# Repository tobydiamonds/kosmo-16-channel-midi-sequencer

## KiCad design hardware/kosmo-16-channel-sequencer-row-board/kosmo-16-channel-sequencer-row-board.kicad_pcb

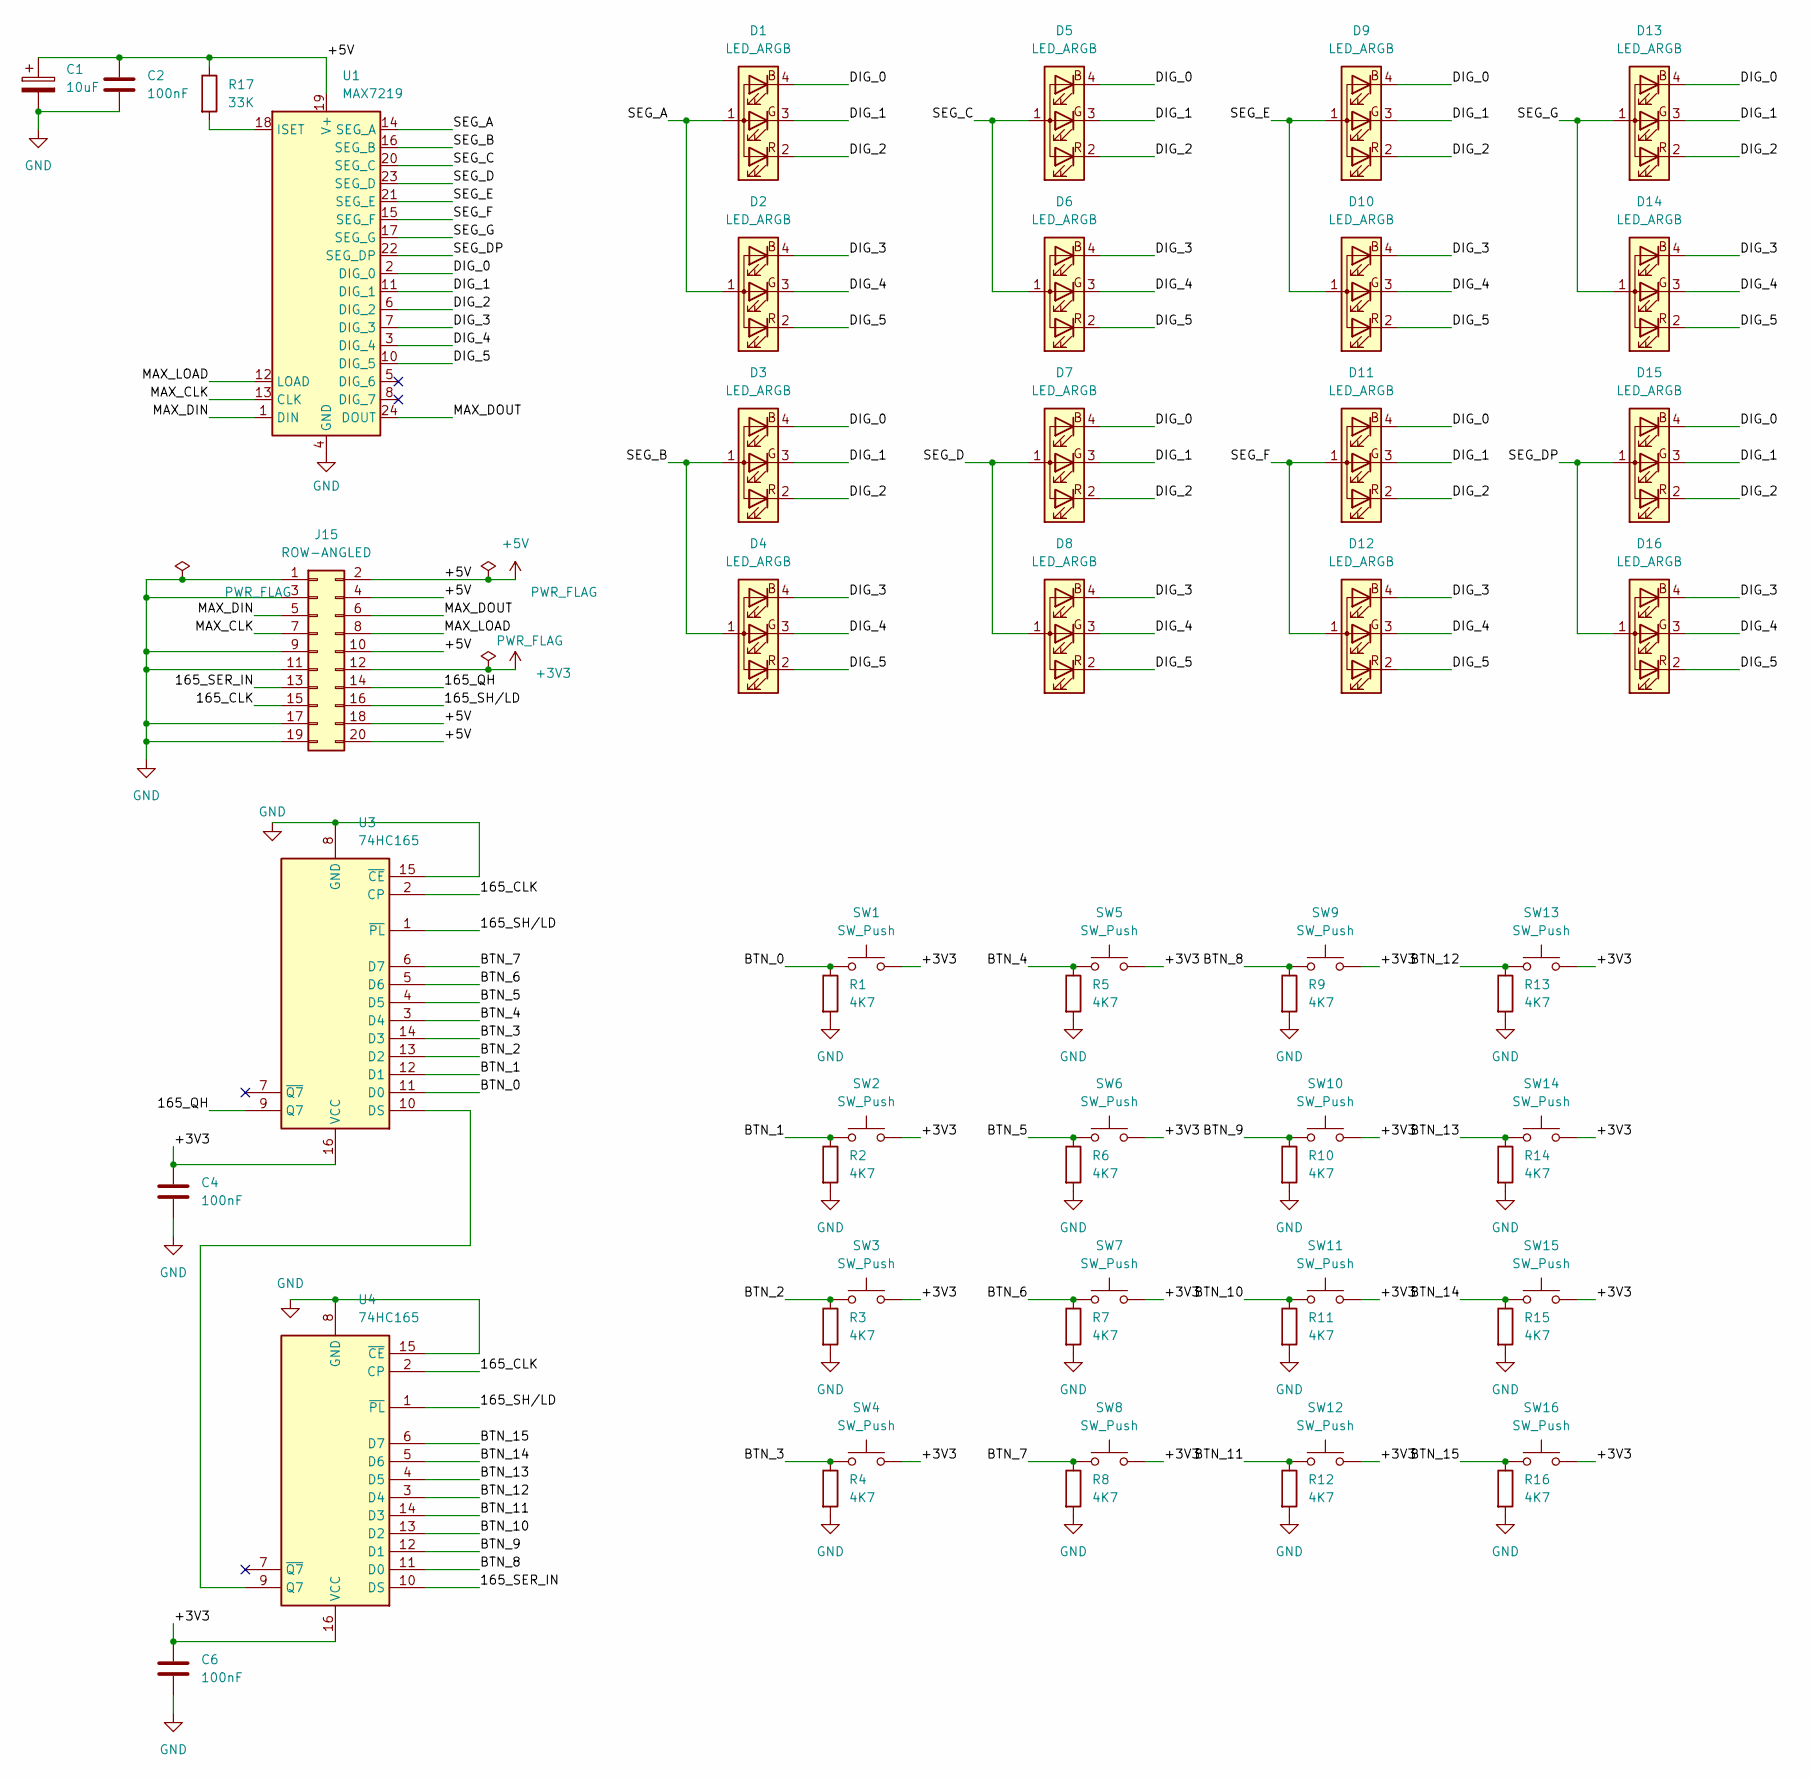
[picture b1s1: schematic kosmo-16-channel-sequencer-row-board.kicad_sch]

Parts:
C1: 10uF; CP_Radial_D6.3mm_P2.50mm
C2, C4, C6: 100nF; C_Disc_D5.0mm_W2.5mm_P5.00mm
D1, D2, D3, D4, D5, D6, D7, D8, D9, D10, D11, D12, D13, D14, D15, D16: LED_ARGB; LED_D5.0mm-4_RGB-common-anode
J15: ROW-ANGLED; PinHeader_2x10_P2.54mm_Vertical
R1, R2, R3, R4, R5, R6, R7, R8, R9, R10, R11, R12, R13, R14, R15, R16: 4K7; R_Axial_DIN0207_L6.3mm_D2.5mm_P7.62mm_Horizontal
R17: 33K; R_Axial_DIN0207_L6.3mm_D2.5mm_P7.62mm_Horizontal
SW1, SW2, SW3, SW4, SW5, SW6, SW7, SW8, SW9, SW10, SW11, SW12, SW13, SW14, SW15, SW16: SW_Push; PinHeader_1x02_P2.54mm_Vertical
U1: MAX7219; SMDIP-24_W15.24mm
U3, U4: 74HC165; DIP-16_W7.62mm

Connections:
+3V3: C4.1, C6.1, J15.12, SW1.2, SW2.2, SW3.2, SW4.2, SW5.2, SW6.2, SW7.2, SW8.2, SW9.2, SW10.2, SW11.2, SW12.2, SW13.2, SW14.2, SW15.2, SW16.2, U3.16 (VCC), U4.16 (VCC)
+5V: C1.1, C2.1, J15.2, J15.4, J15.10, J15.18, J15.20, R17.1, U1.19 (V+)
/165_CLK: J15.15, U3.2 (CP), U4.2 (CP)
/165_QH: J15.14, U3.9 (Q7)
/165_SER_IN: J15.13, U4.10 (DS)
/165_SH/LD: J15.16, U3.1 (~PL), U4.1 (~PL)
/BTN_0: R1.1, SW1.1, U3.11 (D0)
/BTN_1: R2.1, SW2.1, U3.12 (D1)
/BTN_2: R3.1, SW3.1, U3.13 (D2)
/BTN_3: R4.1, SW4.1, U3.14 (D3)
/BTN_4: R5.1, SW5.1, U3.3 (D4)
/BTN_5: R6.1, SW6.1, U3.4 (D5)
/BTN_6: R7.1, SW7.1, U3.5 (D6)
/BTN_7: R8.1, SW8.1, U3.6 (D7)
/BTN_8: R9.1, SW9.1, U4.11 (D0)
/BTN_9: R10.1, SW10.1, U4.12 (D1)
/BTN_10: R11.1, SW11.1, U4.13 (D2)
/BTN_11: R12.1, SW12.1, U4.14 (D3)
/BTN_12: R13.1, SW13.1, U4.3 (D4)
/BTN_13: R14.1, SW14.1, U4.4 (D5)
/BTN_14: R15.1, SW15.1, U4.5 (D6)
/BTN_15: R16.1, SW16.1, U4.6 (D7)
/DIG_0: D1.4 (BK), D3.4 (BK), D5.4 (BK), D7.4 (BK), D9.4 (BK), D11.4 (BK), D13.4 (BK), D15.4 (BK), U1.2 (DIG_0)
/DIG_1: D1.3 (GK), D3.3 (GK), D5.3 (GK), D7.3 (GK), D9.3 (GK), D11.3 (GK), D13.3 (GK), D15.3 (GK), U1.11 (DIG_1)
/DIG_2: D1.2 (RK), D3.2 (RK), D5.2 (RK), D7.2 (RK), D9.2 (RK), D11.2 (RK), D13.2 (RK), D15.2 (RK), U1.6 (DIG_2)
/DIG_3: D2.4 (BK), D4.4 (BK), D6.4 (BK), D8.4 (BK), D10.4 (BK), D12.4 (BK), D14.4 (BK), D16.4 (BK), U1.7 (DIG_3)
/DIG_4: D2.3 (GK), D4.3 (GK), D6.3 (GK), D8.3 (GK), D10.3 (GK), D12.3 (GK), D14.3 (GK), D16.3 (GK), U1.3 (DIG_4)
/DIG_5: D2.2 (RK), D4.2 (RK), D6.2 (RK), D8.2 (RK), D10.2 (RK), D12.2 (RK), D14.2 (RK), D16.2 (RK), U1.10 (DIG_5)
/MAX_CLK: J15.7, U1.13 (CLK)
/MAX_DIN: J15.5, U1.1 (DIN)
/MAX_DOUT: J15.6, U1.24 (DOUT)
/MAX_LOAD: J15.8, U1.12 (LOAD)
/SEG_A: D1.1 (A), D2.1 (A), U1.14 (SEG_A)
/SEG_B: D3.1 (A), D4.1 (A), U1.16 (SEG_B)
/SEG_C: D5.1 (A), D6.1 (A), U1.20 (SEG_C)
/SEG_D: D7.1 (A), D8.1 (A), U1.23 (SEG_D)
/SEG_DP: D15.1 (A), D16.1 (A), U1.22 (SEG_DP)
/SEG_E: D9.1 (A), D10.1 (A), U1.21 (SEG_E)
/SEG_F: D11.1 (A), D12.1 (A), U1.15 (SEG_F)
/SEG_G: D13.1 (A), D14.1 (A), U1.17 (SEG_G)
GND: C1.2, C2.2, C4.2, C6.2, J15.1, J15.3, J15.9, J15.11, J15.17, J15.19, R1.2, R2.2, R3.2, R4.2, R5.2, R6.2, R7.2, R8.2, R9.2, R10.2, R11.2, R12.2, R13.2, R14.2, R15.2, R16.2, U1.4 (GND), U1.9 (GND), U3.8 (GND), U3.15 (~CE), U4.8 (GND), U4.15 (~CE)
unnamed: R17.2, U1.18 (ISET)
unnamed: U3.10 (DS), U4.9 (Q7)

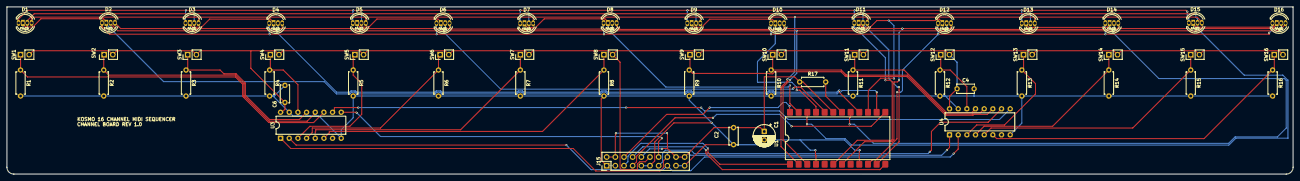
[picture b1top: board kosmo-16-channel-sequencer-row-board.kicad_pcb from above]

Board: 2 copper layers, 377.0 x 49.0 mm, 57 parts (0 on the bottom side), 43 nets.

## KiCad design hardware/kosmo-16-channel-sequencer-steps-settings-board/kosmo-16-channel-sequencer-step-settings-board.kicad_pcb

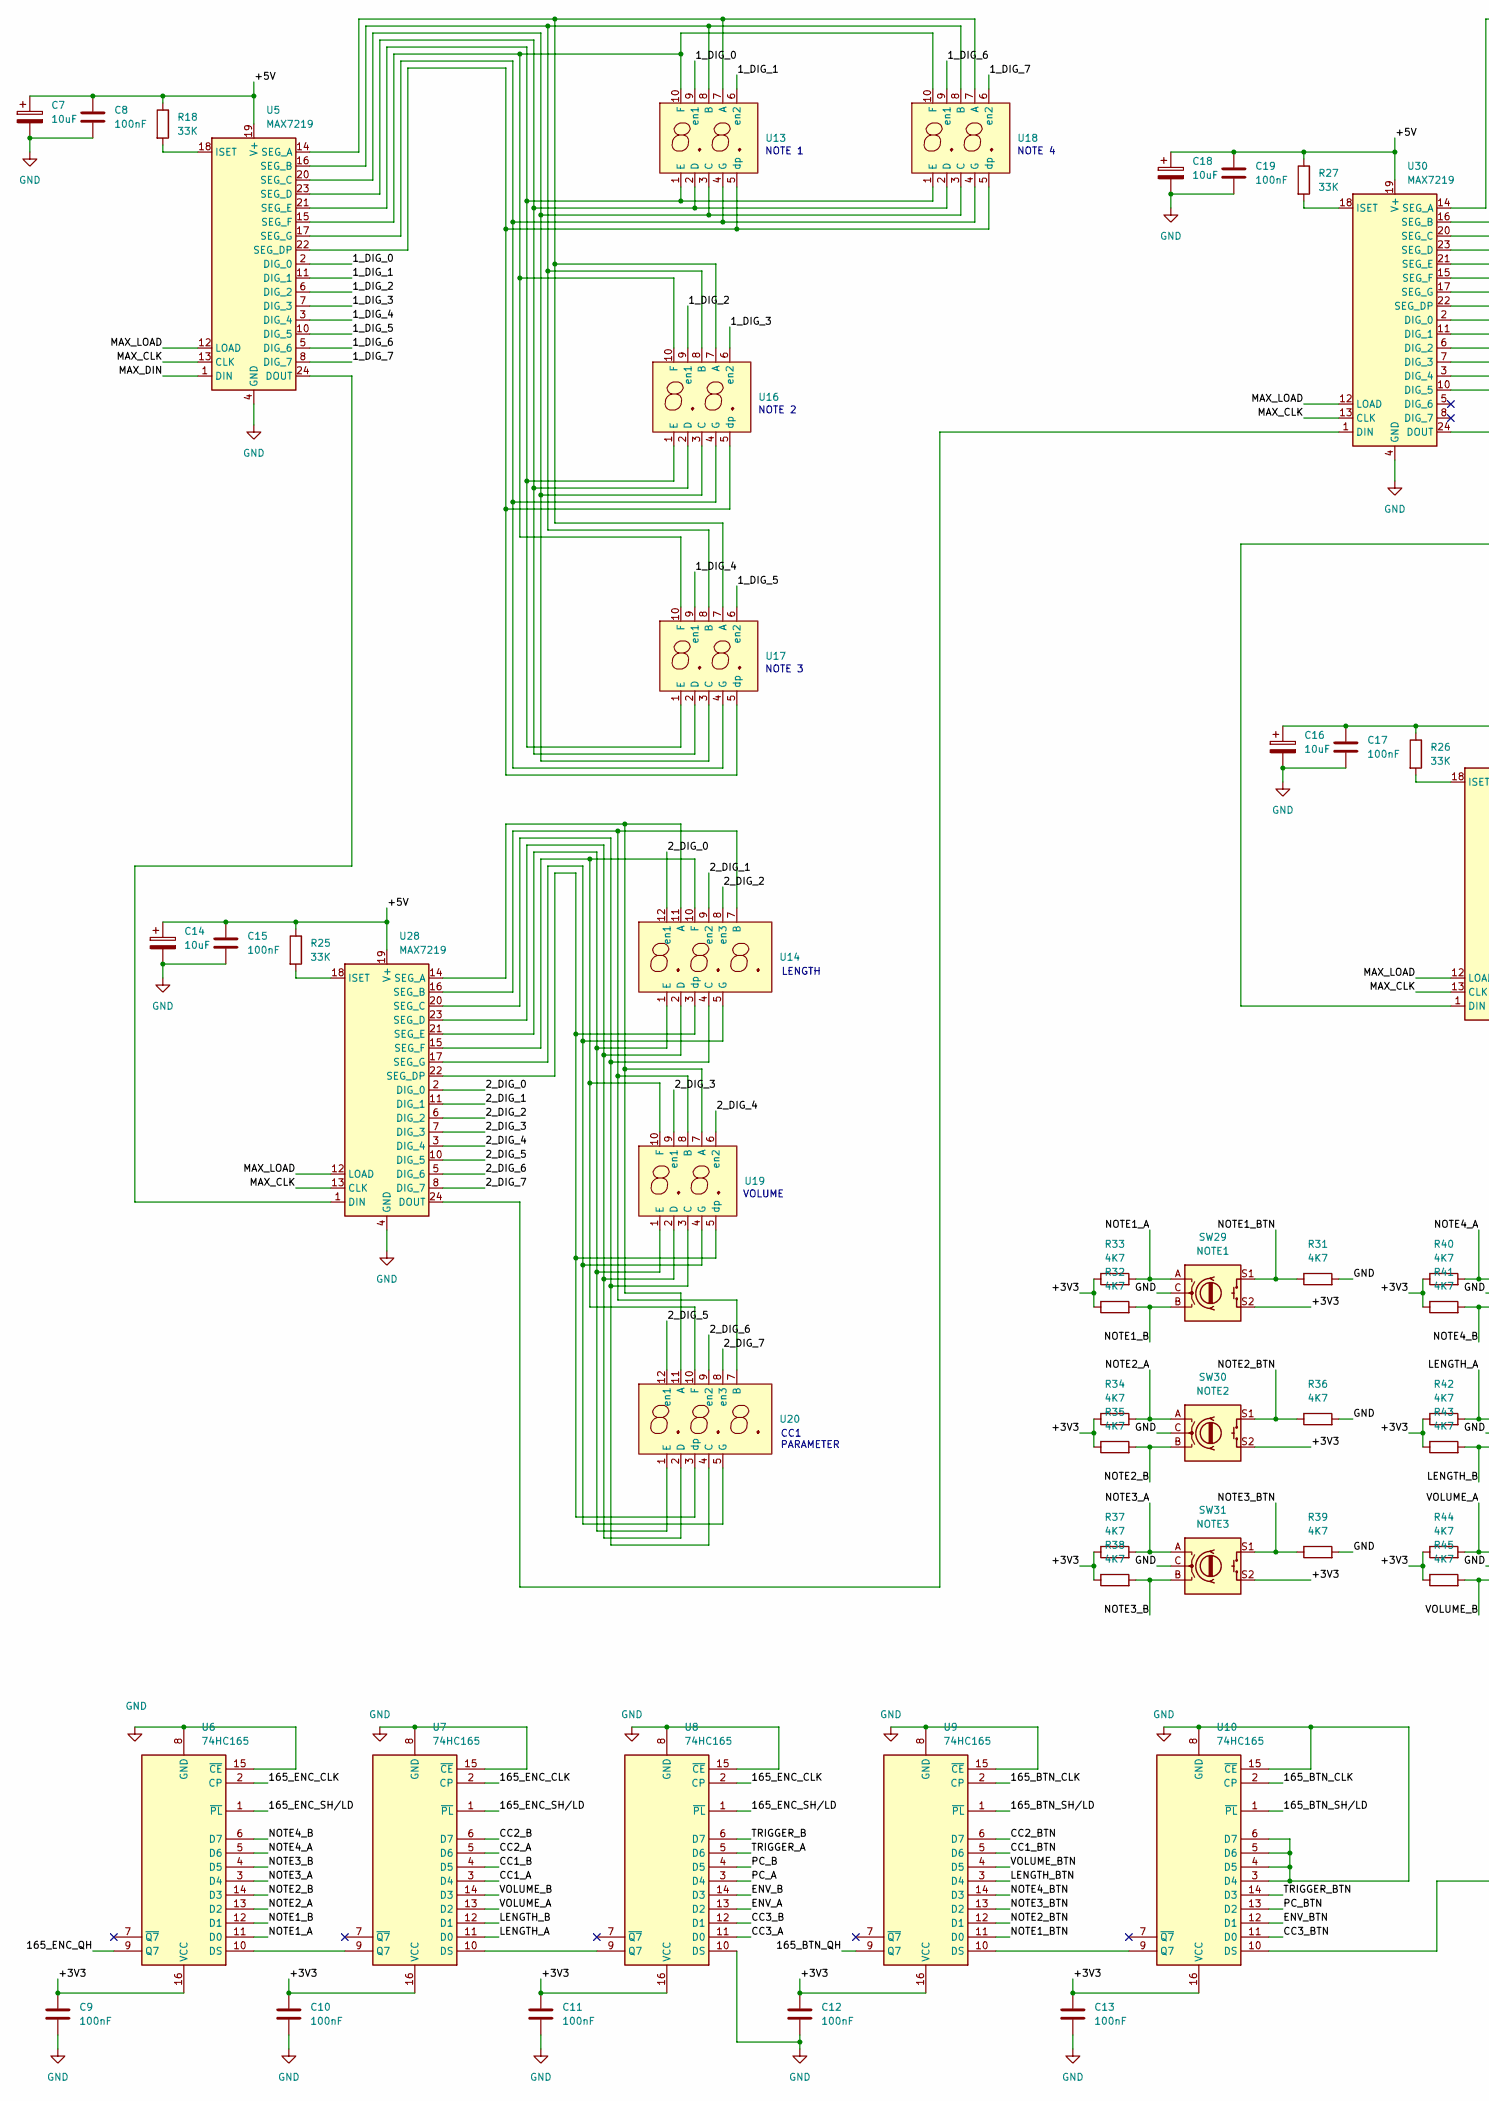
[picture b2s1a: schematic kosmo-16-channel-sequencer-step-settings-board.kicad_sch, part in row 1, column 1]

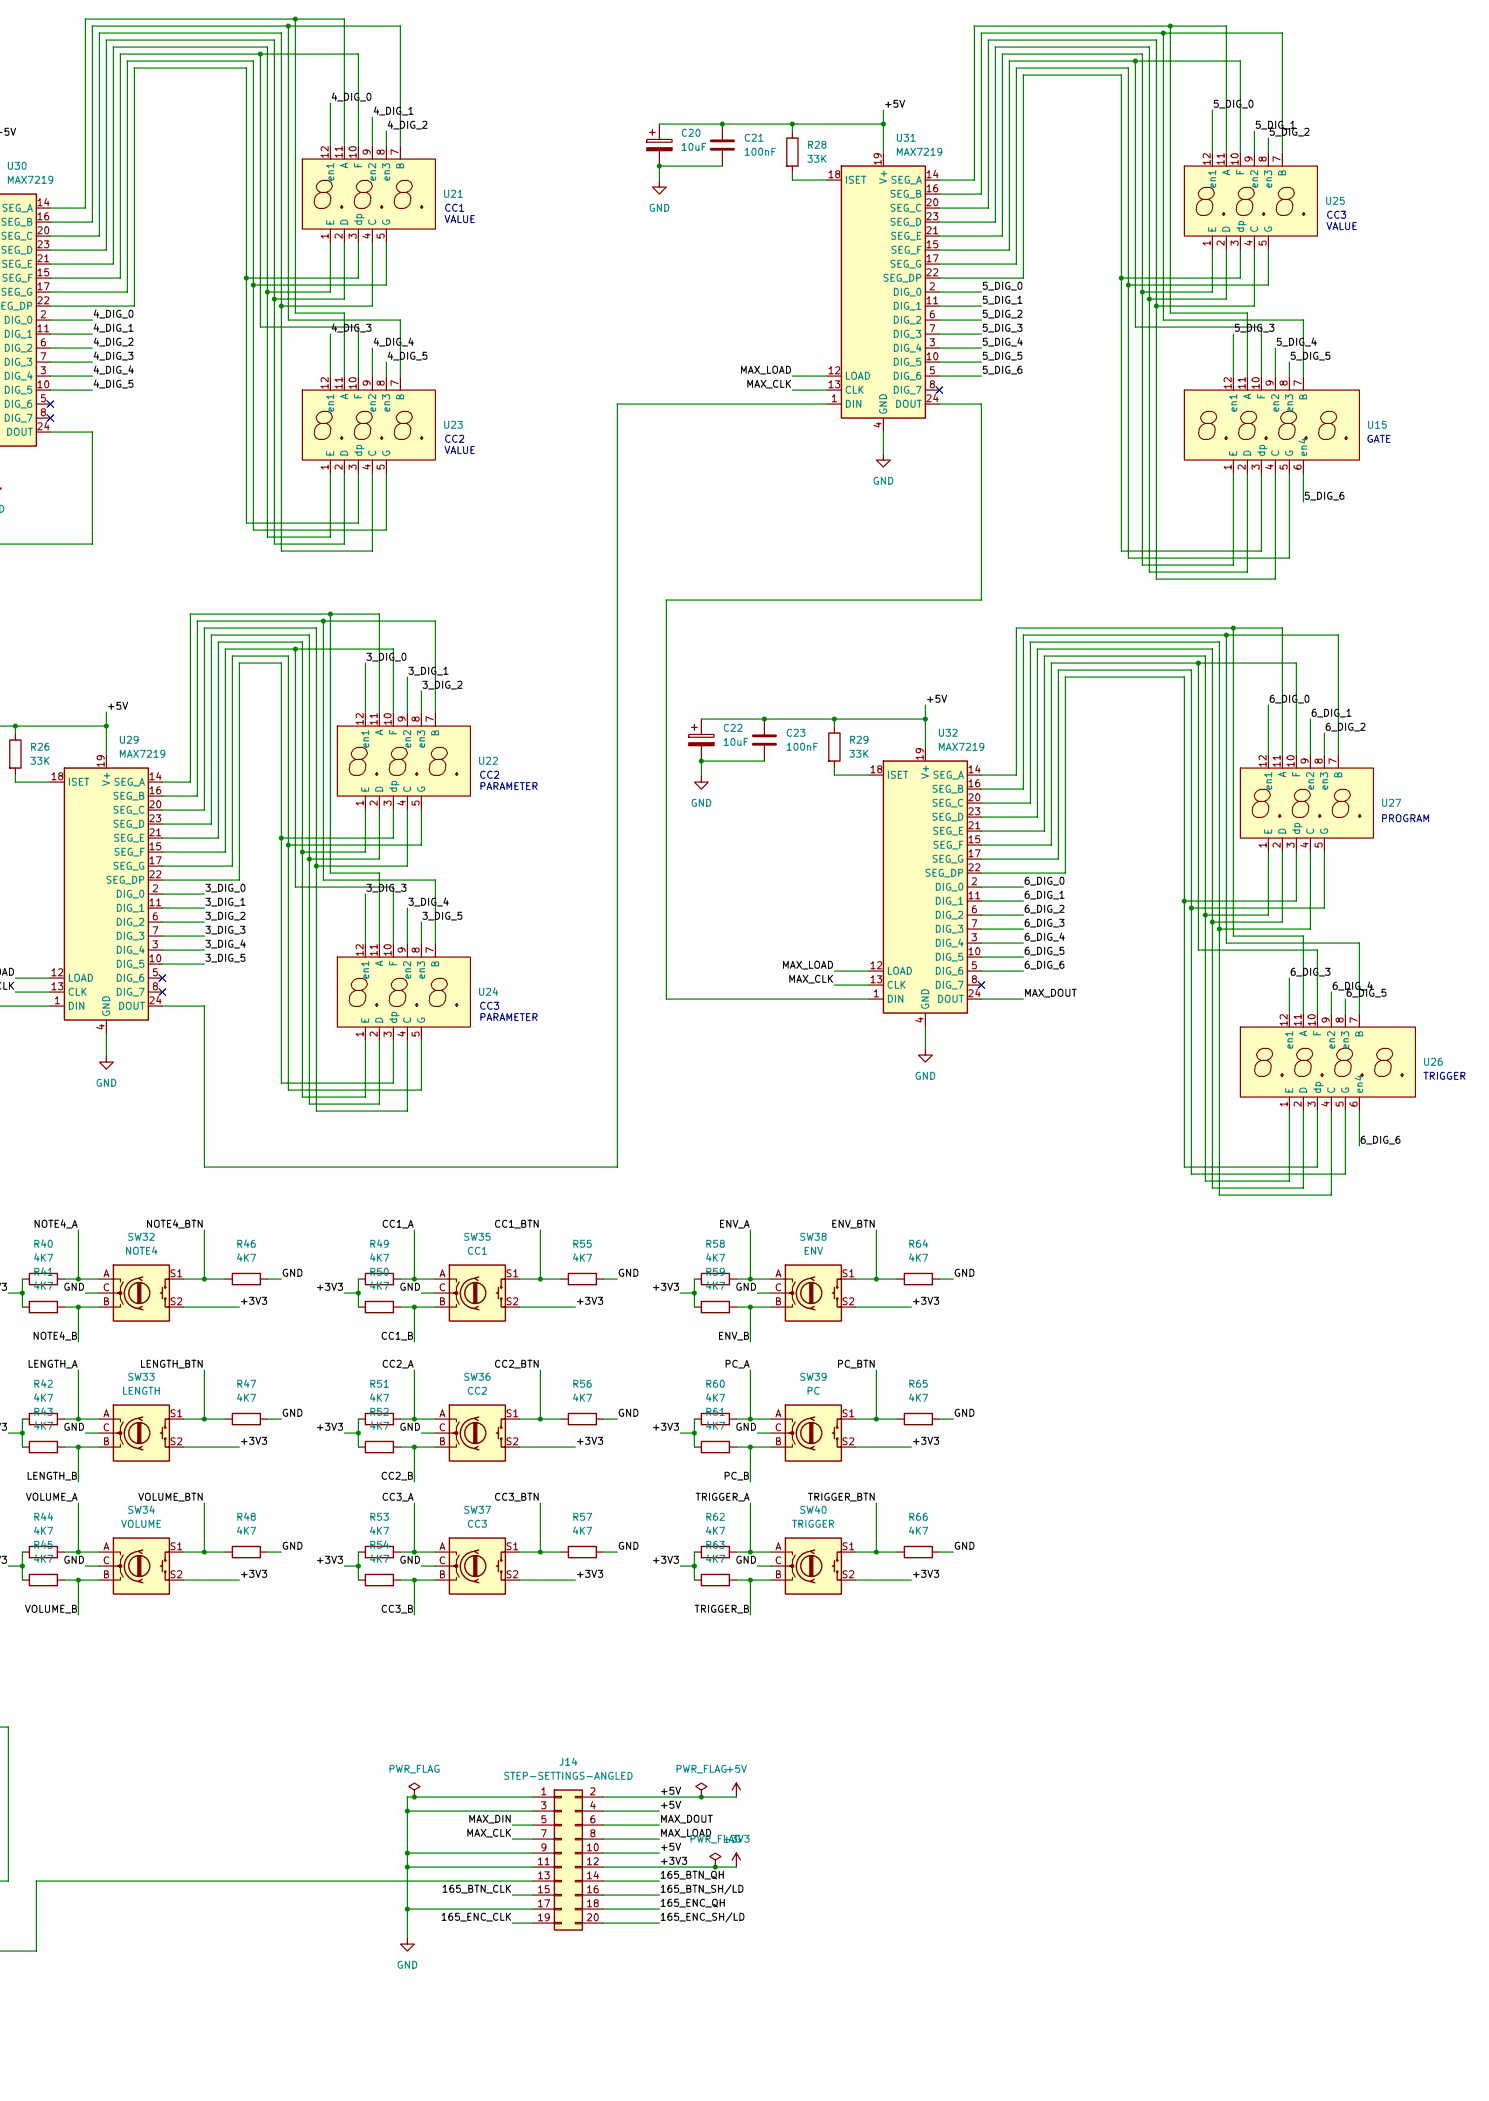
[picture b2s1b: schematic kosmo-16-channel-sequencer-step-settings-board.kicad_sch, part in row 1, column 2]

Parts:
C7, C14, C16, C18, C20, C22: 10uF; CP_Radial_D6.3mm_P2.50mm
C8, C9, C10, C11, C12, C13, C15, C17, C19, C21, C23: 100nF; C_Disc_D5.0mm_W2.5mm_P5.00mm
J14: STEP-SETTINGS-ANGLED; PinHeader_2x10_P2.54mm_Vertical
R18, R25, R26, R27, R28, R29: 33K; R_Axial_DIN0207_L6.3mm_D2.5mm_P7.62mm_Horizontal
R31, R32, R33, R34, R35, R36, R37, R38, R39, R40, R41, R42, R43, R44, R45, R46, R47, R48, R49, R50, R51, R52, R53, R54, R55, R56, R57, R58, R59, R60, R61, R62, R63, R64, R65, R66: 4K7; R_Axial_DIN0207_L6.3mm_D2.5mm_P7.62mm_Horizontal
SW29: NOTE1; RotaryEncoder_Bourns_Vertical_PEC12R-3x17F-Sxxxx
SW30: NOTE2; RotaryEncoder_Bourns_Vertical_PEC12R-3x17F-Sxxxx
SW31: NOTE3; RotaryEncoder_Bourns_Vertical_PEC12R-3x17F-Sxxxx
SW32: NOTE4; RotaryEncoder_Bourns_Vertical_PEC12R-3x17F-Sxxxx
SW33: LENGTH; RotaryEncoder_Bourns_Vertical_PEC12R-3x17F-Sxxxx
SW34: VOLUME; RotaryEncoder_Bourns_Vertical_PEC12R-3x17F-Sxxxx
SW35: CC1; RotaryEncoder_Bourns_Vertical_PEC12R-3x17F-Sxxxx
SW36: CC2; RotaryEncoder_Bourns_Vertical_PEC12R-3x17F-Sxxxx
SW37: CC3; RotaryEncoder_Bourns_Vertical_PEC12R-3x17F-Sxxxx
SW38: ENV; RotaryEncoder_Bourns_Vertical_PEC12R-3x17F-Sxxxx
SW39: PC; RotaryEncoder_Bourns_Vertical_PEC12R-3x17F-Sxxxx
SW40: TRIGGER; RotaryEncoder_Bourns_Vertical_PEC12R-3x17F-Sxxxx
U5, U28, U29, U30, U31, U32: MAX7219; SMDIP-24_W15.24mm
U6, U7, U8, U9, U10: 74HC165; DIP-16_W7.62mm
U13, U16, U17, U18, U19: DIP-10_W7.62mm
U14, U15, U20, U21, U22, U23, U24, U25, U26, U27: DIP-12_W7.62mm

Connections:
+3V3: C9.1, C10.1, C11.1, C12.1, C13.1, J14.12, R32.1, R33.1, R34.1, R35.1, R37.1, R38.1, R40.1, R41.1, R42.1, R43.1, R44.1, R45.1, R49.1, R50.1, R51.1, R52.1, R53.1, R54.1, R58.1, R59.1, R60.1, R61.1, R62.1, R63.1, SW29.S2, SW30.S2, SW31.S2, SW32.S2, SW33.S2, SW34.S2, SW35.S2, SW36.S2, SW37.S2, SW38.S2, SW39.S2, SW40.S2, U6.16 (VCC), U7.16 (VCC), U8.16 (VCC), U9.16 (VCC), U10.16 (VCC)
+5V: C7.1, C8.1, C14.1, C15.1, C16.1, C17.1, C18.1, C19.1, C20.1, C21.1, C22.1, C23.1, J14.2, J14.4, J14.10, R18.1, R25.1, R26.1, R27.1, R28.1, R29.1, U5.19 (V+), U28.19 (V+), U29.19 (V+), U30.19 (V+), U31.19 (V+), U32.19 (V+)
/1_DIG_0: U5.2 (DIG_0), U13.9 (en1)
/1_DIG_1: U5.11 (DIG_1), U13.6 (en2)
/1_DIG_2: U5.6 (DIG_2), U16.9 (en1)
/1_DIG_3: U5.7 (DIG_3), U16.6 (en2)
/1_DIG_4: U5.3 (DIG_4), U17.9 (en1)
/1_DIG_5: U5.10 (DIG_5), U17.6 (en2)
/1_DIG_6: U5.5 (DIG_6), U18.9 (en1)
/1_DIG_7: U5.8 (DIG_7), U18.6 (en2)
/2_DIG_0: U14.12 (en1), U28.2 (DIG_0)
/2_DIG_1: U14.9 (en2), U28.11 (DIG_1)
/2_DIG_2: U14.8 (en3), U28.6 (DIG_2)
/2_DIG_3: U19.9 (en1), U28.7 (DIG_3)
/2_DIG_4: U19.6 (en2), U28.3 (DIG_4)
/2_DIG_5: U20.12 (en1), U28.10 (DIG_5)
/2_DIG_6: U20.9 (en2), U28.5 (DIG_6)
/2_DIG_7: U20.8 (en3), U28.8 (DIG_7)
/3_DIG_0: U22.12 (en1), U29.2 (DIG_0)
/3_DIG_1: U22.9 (en2), U29.11 (DIG_1)
/3_DIG_2: U22.8 (en3), U29.6 (DIG_2)
/3_DIG_3: U24.12 (en1), U29.7 (DIG_3)
/3_DIG_4: U24.9 (en2), U29.3 (DIG_4)
/3_DIG_5: U24.8 (en3), U29.10 (DIG_5)
/4_DIG_0: U21.12 (en1), U30.2 (DIG_0)
/4_DIG_1: U21.9 (en2), U30.11 (DIG_1)
/4_DIG_2: U21.8 (en3), U30.6 (DIG_2)
/4_DIG_3: U23.12 (en1), U30.7 (DIG_3)
/4_DIG_4: U23.9 (en2), U30.3 (DIG_4)
/4_DIG_5: U23.8 (en3), U30.10 (DIG_5)
/5_DIG_0: U25.12 (en1), U31.2 (DIG_0)
/5_DIG_1: U25.9 (en2), U31.11 (DIG_1)
/5_DIG_2: U25.8 (en3), U31.6 (DIG_2)
/5_DIG_3: U15.12 (en1), U31.7 (DIG_3)
/5_DIG_4: U15.9 (en2), U31.3 (DIG_4)
/5_DIG_5: U15.8 (en3), U31.10 (DIG_5)
/5_DIG_6: U15.6 (en4), U31.5 (DIG_6)
/6_DIG_0: U27.12 (en1), U32.2 (DIG_0)
/6_DIG_1: U27.9 (en2), U32.11 (DIG_1)
/6_DIG_2: U27.8 (en3), U32.6 (DIG_2)
/6_DIG_3: U26.12 (en1), U32.7 (DIG_3)
/6_DIG_4: U26.9 (en2), U32.3 (DIG_4)
/6_DIG_5: U26.8 (en3), U32.10 (DIG_5)
/6_DIG_6: U26.6 (en4), U32.5 (DIG_6)
/165_BTN_CLK: J14.15, U9.2 (CP), U10.2 (CP)
/165_BTN_QH: J14.14, U9.9 (Q7)
/165_BTN_SH/LD: J14.16, U9.1 (~PL), U10.1 (~PL)
/165_ENC_CLK: J14.19, U6.2 (CP), U7.2 (CP), U8.2 (CP)
/165_ENC_QH: J14.18, U6.9 (Q7)
/165_ENC_SH/LD: J14.20, U6.1 (~PL), U7.1 (~PL), U8.1 (~PL)
/CC1_A: R49.2, SW35.A, U7.3 (D4)
/CC1_B: R50.2, SW35.B, U7.4 (D5)
/CC1_BTN: R55.1, SW35.S1, U9.5 (D6)
/CC2_A: R51.2, SW36.A, U7.5 (D6)
/CC2_B: R52.2, SW36.B, U7.6 (D7)
/CC2_BTN: R56.1, SW36.S1, U9.6 (D7)
/CC3_A: R53.2, SW37.A, U8.11 (D0)
/CC3_B: R54.2, SW37.B, U8.12 (D1)
/CC3_BTN: R57.1, SW37.S1, U10.11 (D0)
/ENV_A: R58.2, SW38.A, U8.13 (D2)
/ENV_B: R59.2, SW38.B, U8.14 (D3)
/ENV_BTN: R64.1, SW38.S1, U10.12 (D1)
/LENGTH_A: R42.2, SW33.A, U7.11 (D0)
/LENGTH_B: R43.2, SW33.B, U7.12 (D1)
/LENGTH_BTN: R47.1, SW33.S1, U9.3 (D4)
/MAX_CLK: J14.7, U5.13 (CLK), U28.13 (CLK), U29.13 (CLK), U30.13 (CLK), U31.13 (CLK), U32.13 (CLK)
/MAX_DIN: J14.5, U5.1 (DIN)
/MAX_DOUT: J14.6, U32.24 (DOUT)
/MAX_LOAD: J14.8, U5.12 (LOAD), U28.12 (LOAD), U29.12 (LOAD), U30.12 (LOAD), U31.12 (LOAD), U32.12 (LOAD)
/NOTE1_A: R33.2, SW29.A, U6.11 (D0)
/NOTE1_B: R32.2, SW29.B, U6.12 (D1)
/NOTE1_BTN: R31.1, SW29.S1, U9.11 (D0)
/NOTE2_A: R34.2, SW30.A, U6.13 (D2)
/NOTE2_B: R35.2, SW30.B, U6.14 (D3)
/NOTE2_BTN: R36.1, SW30.S1, U9.12 (D1)
/NOTE3_A: R37.2, SW31.A, U6.3 (D4)
/NOTE3_B: R38.2, SW31.B, U6.4 (D5)
/NOTE3_BTN: R39.1, SW31.S1, U9.13 (D2)
/NOTE4_A: R40.2, SW32.A, U6.5 (D6)
/NOTE4_B: R41.2, SW32.B, U6.6 (D7)
/NOTE4_BTN: R46.1, SW32.S1, U9.14 (D3)
/PC_A: R60.2, SW39.A, U8.3 (D4)
/PC_B: R61.2, SW39.B, U8.4 (D5)
/PC_BTN: R65.1, SW39.S1, U10.13 (D2)
/TRIGGER_A: R62.2, SW40.A, U8.5 (D6)
/TRIGGER_B: R63.2, SW40.B, U8.6 (D7)
/TRIGGER_BTN: R66.1, SW40.S1, U10.14 (D3)
/VOLUME_A: R44.2, SW34.A, U7.13 (D2)
/VOLUME_B: R45.2, SW34.B, U7.14 (D3)
/VOLUME_BTN: R48.1, SW34.S1, U9.4 (D5)
GND: C7.2, C8.2, C9.2, C10.2, C11.2, C12.2, C13.2, C14.2, C15.2, C16.2, C17.2, C18.2, C19.2, C20.2, C21.2, C22.2, C23.2, J14.1, J14.3, J14.9, J14.11, J14.17, R31.2, R36.2, R39.2, R46.2, R47.2, R48.2, R55.2, R56.2, R57.2, R64.2, R65.2, R66.2, SW29.C, SW30.C, SW31.C, SW32.C, SW33.C, SW34.C, SW35.C, SW36.C, SW37.C, SW38.C, SW39.C, SW40.C, U5.4 (GND), U5.9 (GND), U6.8 (GND), U6.15 (~CE), U7.8 (GND), U7.15 (~CE), U8.8 (GND), U8.10 (DS), U8.15 (~CE), U9.8 (GND), U9.15 (~CE), U10.3 (D4), U10.4 (D5), U10.5 (D6), U10.6 (D7), U10.8 (GND), U10.15 (~CE), U28.4 (GND), U28.9 (GND), U29.4 (GND), U29.9 (GND), U30.4 (GND), U30.9 (GND), U31.4 (GND), U31.9 (GND), U32.4 (GND), U32.9 (GND)
unnamed: J14.13, U10.10 (DS)
unnamed: R18.2, U5.18 (ISET)
unnamed: U6.10 (DS), U7.9 (Q7)
unnamed: U7.10 (DS), U8.9 (Q7)
unnamed: U9.10 (DS), U10.9 (Q7)
unnamed: U5.14 (SEG_A), U13.7 (A), U16.7 (A), U17.7 (A), U18.7 (A)
unnamed: U5.16 (SEG_B), U13.8 (B), U16.8 (B), U17.8 (B), U18.8 (B)
unnamed: U5.20 (SEG_C), U13.3 (C), U16.3 (C), U17.3 (C), U18.3 (C)
unnamed: U5.23 (SEG_D), U13.2 (D), U16.2 (D), U17.2 (D), U18.2 (D)
unnamed: U5.21 (SEG_E), U13.1 (E), U16.1 (E), U17.1 (E), U18.1 (E)
unnamed: U5.15 (SEG_F), U13.10 (F), U16.10 (F), U17.10 (F), U18.10 (F)
unnamed: U5.17 (SEG_G), U13.4 (G), U16.4 (G), U17.4 (G), U18.4 (G)
unnamed: U5.22 (SEG_DP), U13.5 (dp), U16.5 (dp), U17.5 (dp), U18.5 (dp)
unnamed: U14.11 (A), U19.7 (A), U20.11 (A), U28.14 (SEG_A)
unnamed: U14.7 (B), U19.8 (B), U20.7 (B), U28.16 (SEG_B)
unnamed: U14.4 (C), U19.3 (C), U20.4 (C), U28.20 (SEG_C)
unnamed: U14.2 (D), U19.2 (D), U20.2 (D), U28.23 (SEG_D)
unnamed: U14.1 (E), U19.1 (E), U20.1 (E), U28.21 (SEG_E)
unnamed: U14.10 (F), U19.10 (F), U20.10 (F), U28.15 (SEG_F)
unnamed: U14.5 (G), U19.4 (G), U20.5 (G), U28.17 (SEG_G)
unnamed: U14.3 (dp), U19.5 (dp), U20.3 (dp), U28.22 (SEG_DP)
unnamed: U15.11 (A), U25.11 (A), U31.14 (SEG_A)
unnamed: U15.7 (B), U25.7 (B), U31.16 (SEG_B)
unnamed: U15.4 (C), U25.4 (C), U31.20 (SEG_C)
unnamed: U15.2 (D), U25.2 (D), U31.23 (SEG_D)
unnamed: U15.1 (E), U25.1 (E), U31.21 (SEG_E)
unnamed: U15.10 (F), U25.10 (F), U31.15 (SEG_F)
unnamed: U15.5 (G), U25.5 (G), U31.17 (SEG_G)
unnamed: U15.3 (dp), U25.3 (dp), U31.22 (SEG_DP)
unnamed: U21.11 (A), U23.11 (A), U30.14 (SEG_A)
unnamed: U21.7 (B), U23.7 (B), U30.16 (SEG_B)
unnamed: U21.4 (C), U23.4 (C), U30.20 (SEG_C)
unnamed: U21.2 (D), U23.2 (D), U30.23 (SEG_D)
unnamed: U21.1 (E), U23.1 (E), U30.21 (SEG_E)
unnamed: U21.10 (F), U23.10 (F), U30.15 (SEG_F)
unnamed: U21.5 (G), U23.5 (G), U30.17 (SEG_G)
unnamed: U21.3 (dp), U23.3 (dp), U30.22 (SEG_DP)
unnamed: U22.11 (A), U24.11 (A), U29.14 (SEG_A)
unnamed: U22.7 (B), U24.7 (B), U29.16 (SEG_B)
unnamed: U22.4 (C), U24.4 (C), U29.20 (SEG_C)
unnamed: U22.2 (D), U24.2 (D), U29.23 (SEG_D)
unnamed: U22.1 (E), U24.1 (E), U29.21 (SEG_E)
unnamed: U22.10 (F), U24.10 (F), U29.15 (SEG_F)
unnamed: U22.5 (G), U24.5 (G), U29.17 (SEG_G)
unnamed: U22.3 (dp), U24.3 (dp), U29.22 (SEG_DP)
unnamed: U26.11 (A), U27.11 (A), U32.14 (SEG_A)
unnamed: U26.7 (B), U27.7 (B), U32.16 (SEG_B)
unnamed: U26.4 (C), U27.4 (C), U32.20 (SEG_C)
unnamed: U26.2 (D), U27.2 (D), U32.23 (SEG_D)
unnamed: U26.1 (E), U27.1 (E), U32.21 (SEG_E)
unnamed: U26.10 (F), U27.10 (F), U32.15 (SEG_F)
unnamed: U26.5 (G), U27.5 (G), U32.17 (SEG_G)
unnamed: U26.3 (dp), U27.3 (dp), U32.22 (SEG_DP)
unnamed: U5.24 (DOUT), U28.1 (DIN)
unnamed: U28.24 (DOUT), U30.1 (DIN)
unnamed: R25.2, U28.18 (ISET)
unnamed: U29.1 (DIN), U30.24 (DOUT)
unnamed: U29.24 (DOUT), U31.1 (DIN)
unnamed: R26.2, U29.18 (ISET)
unnamed: R27.2, U30.18 (ISET)
unnamed: U31.24 (DOUT), U32.1 (DIN)
unnamed: R28.2, U31.18 (ISET)
unnamed: R29.2, U32.18 (ISET)

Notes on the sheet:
GATE
NOTE 4
NOTE 1
CC1 PARAMETER
NOTE 2
VOLUME
CC3 VALUE
PROGRAM
CC3 PARAMETER
TRIGGER
LENGTH
CC2 VALUE
CC1 VALUE
NOTE 3
CC2 PARAMETER

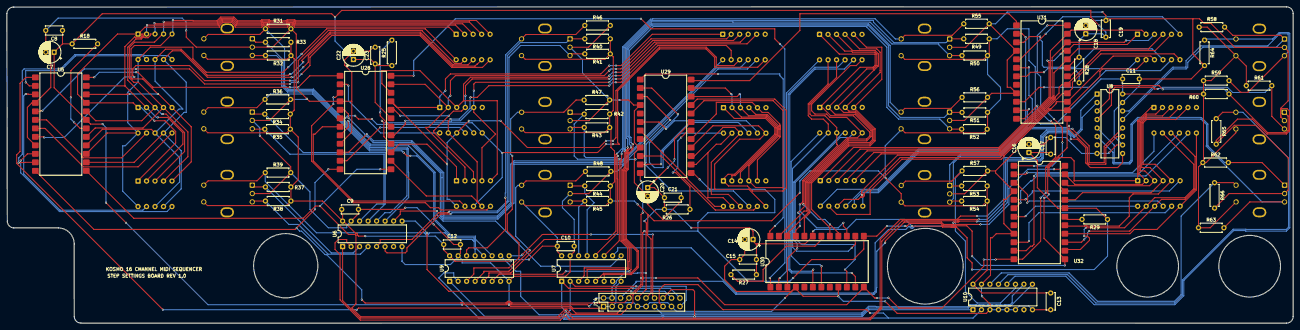
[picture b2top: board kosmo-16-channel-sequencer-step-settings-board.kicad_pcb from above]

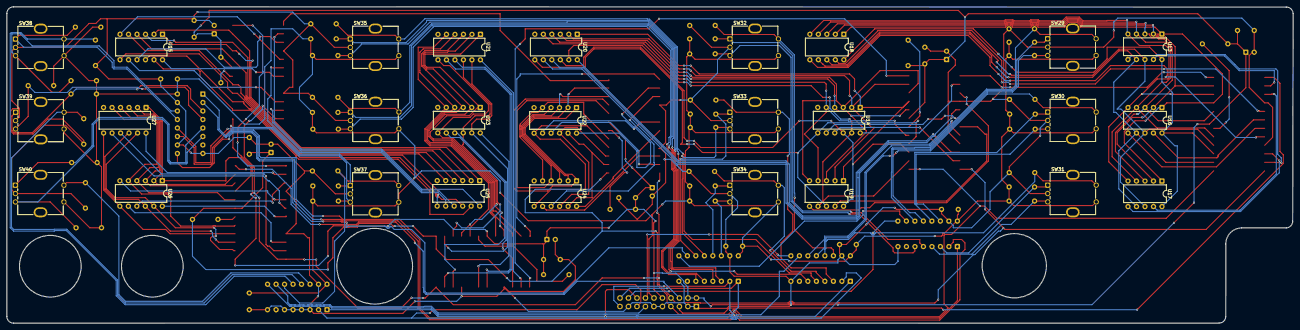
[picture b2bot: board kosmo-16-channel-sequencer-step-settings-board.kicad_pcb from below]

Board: 2 copper layers, 384.6 x 94.6 mm, 98 parts (27 on the bottom side), 154 nets.
